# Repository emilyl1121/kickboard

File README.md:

# kickboard
This repository is an attempt of recreating a portable seiko kickboard designed for recording swimmers' times. Part of my school mastery project.

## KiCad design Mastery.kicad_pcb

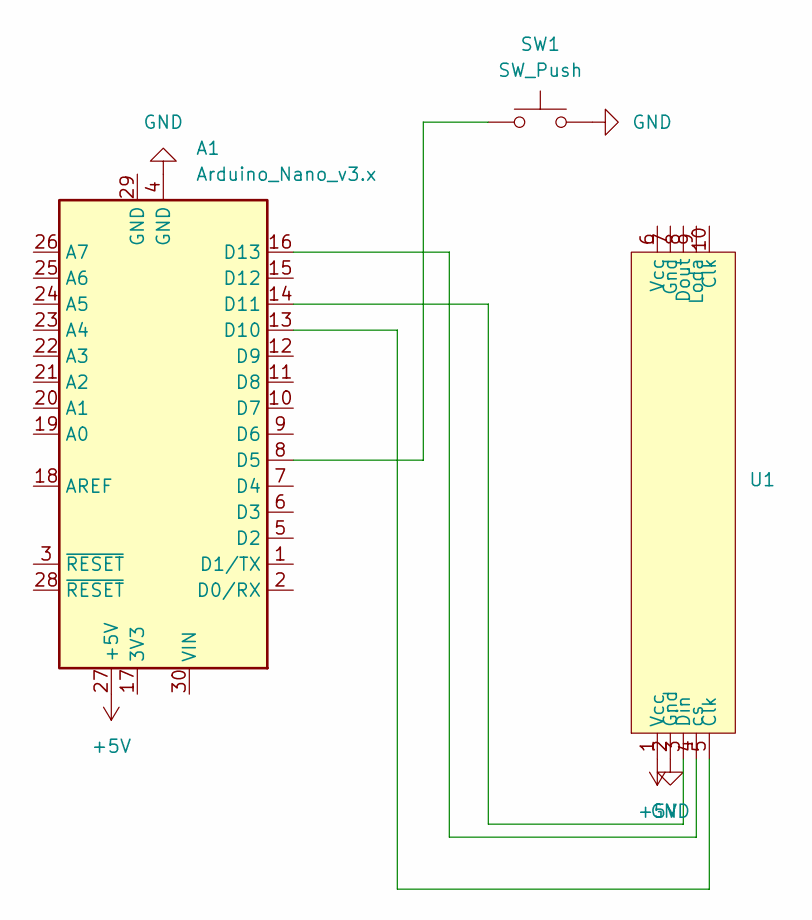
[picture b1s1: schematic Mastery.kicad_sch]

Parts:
A1: Arduino_Nano_v3.x; Arduino_Nano
SW1: SW_Push; SW_PUSH-12mm
U1: 7segment8digit

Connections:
+5V: A1.27 (+5V), U1.1 (Vcc)
GND: A1.4 (GND), SW1.2, U1.2 (Gnd)
unnamed: A1.8 (D5), SW1.1
unnamed: A1.13 (D10), U1.5 (Clk)
unnamed: A1.14 (D11), U1.3 (Din)
unnamed: A1.16 (D13), U1.4 (cs)

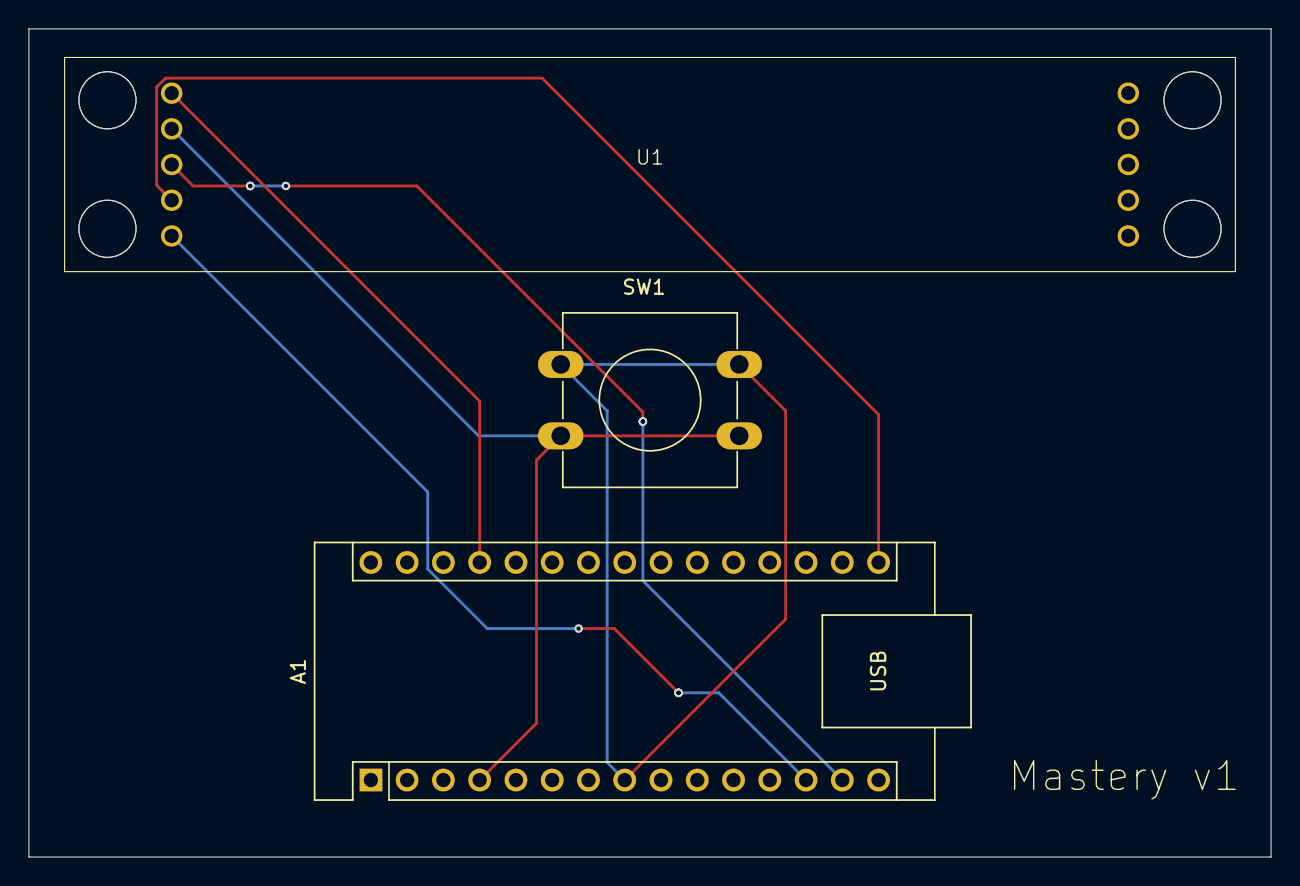
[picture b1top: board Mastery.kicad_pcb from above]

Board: 2 copper layers, 87.0 x 58.0 mm, 3 parts (0 on the bottom side), 6 nets.

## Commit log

2026-02-09 Expand devlog with research and testing updates
    Added detailed entries for project research, parts selection, schematic layout, and testing results.
